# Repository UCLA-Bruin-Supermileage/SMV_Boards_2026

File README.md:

# SMV_Boards_2026
SMV low-voltage projects for 2025-2026

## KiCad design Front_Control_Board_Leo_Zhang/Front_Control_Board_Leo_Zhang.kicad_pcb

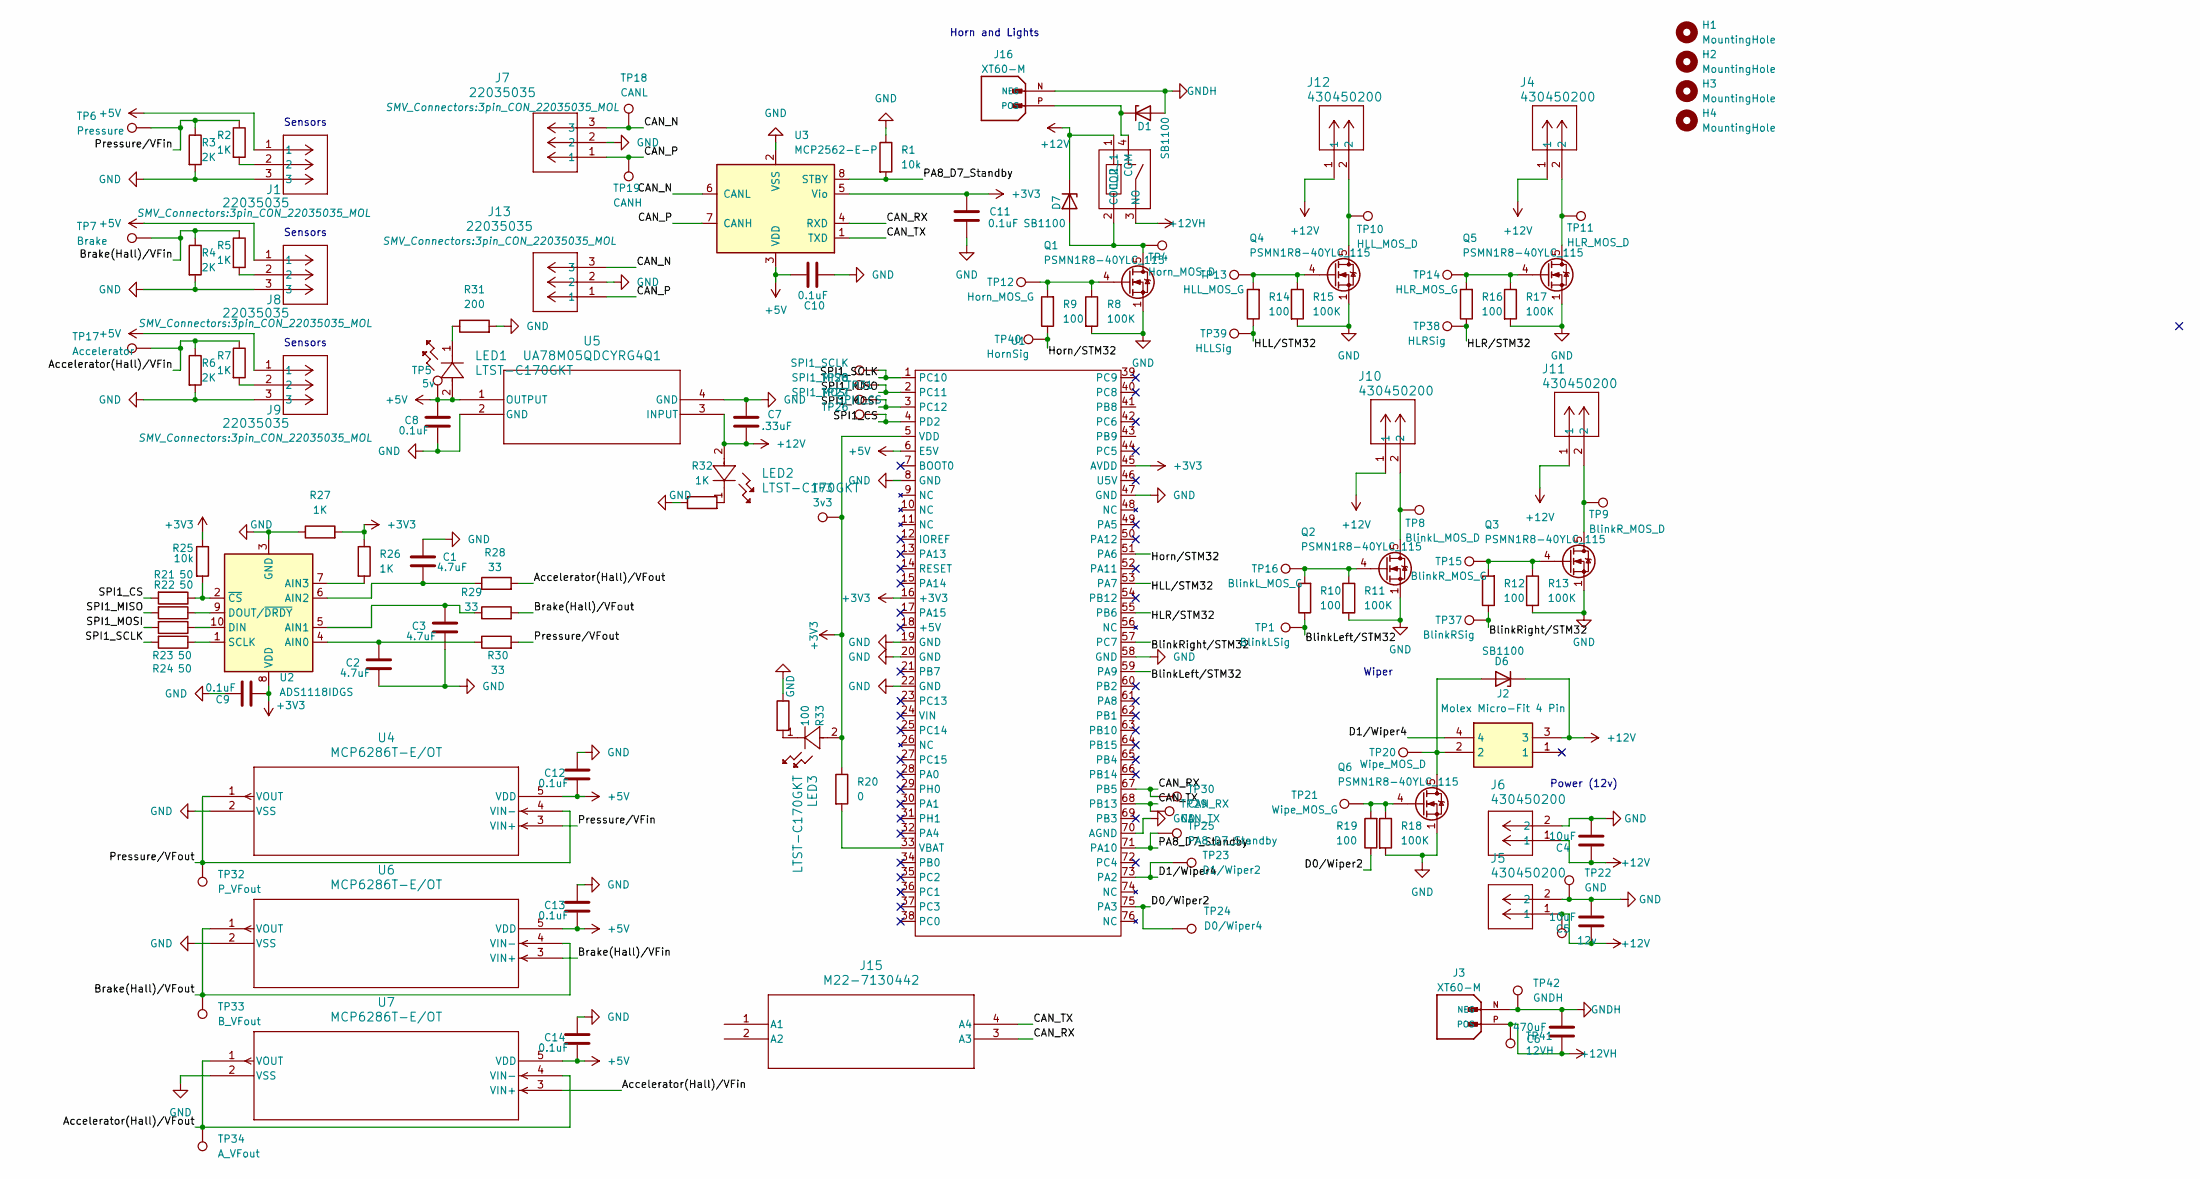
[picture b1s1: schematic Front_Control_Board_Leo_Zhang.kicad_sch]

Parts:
C1, C2, C3: 4.7uF; C_0805_2012Metric
C4, C5: 10uF; CP_Radial_D5.0mm_P2.00mm
C6: 470uF; CP_Radial_D16.0mm_P7.50mm
C7: .33uF; C_0805_2012Metric
C8, C9, C10, C11, C12, C13, C14: 0.1uF; C_0805_2012Metric
D1, D6, D7: SB1100; DO-41_DIO
H1, H2, H3, H4: MountingHole; MountingHole_3.2mm_M3
J1, J7, J8, J9, J13: 22035035; 3pin_CON_22035035_MOL
J2: Molex Micro-Fit 4 Pin; 4_pin0430450401; Manufacturer_Part_Number 0430450401
J3, J16: XT60-M; AMASS_XT60-M; PARTREV V1.2
J4, J5, J6, J10, J11, J12: 430450200; CONN_SD-43045-001_02_MOL
J15: M22-7130442; M22-7130442_TYC
LED1, LED2, LED3: LTST-C170GKT; LED_D3.0mm
Q1, Q2, Q3, Q4, Q5, Q6: PSMN1R8-40YLC_115; LFPAK56_SOT669_NEX
R1, R25: 10k; R_0805_2012Metric
R2, R5, R7, R26, R27, R32: 1K; R_0805_2012Metric
R3, R4, R6: 2K; R_0805_2012Metric
R8, R11, R13, R15, R17, R18: 100K; R_0805_2012Metric
R9, R10, R12, R14, R16, R19, R33: 100; R_0805_2012Metric
R20: 0; R_0805_2012Metric
R21, R22, R23, R24: 50; R_0805_2012Metric
R28, R29, R30: 33; R_0805_2012Metric
R31: 200; R_0805_2012Metric
TP1: BlinkLSig; ValueTestPoint_Pad_D1.0mm
TP2: 12v; ValueTestPoint_Pad_D1.0mm
TP3: 3v3; ValueTestPoint_Pad_D1.0mm
TP4: Horn_MOS_D; ValueTestPoint_Pad_D1.0mm
TP5: 5v; ValueTestPoint_Pad_D1.0mm
TP6: Pressure; ValueTestPoint_Pad_D1.0mm
TP7: Brake; ValueTestPoint_Pad_D1.0mm
TP8: BlinkL_MOS_D; ValueTestPoint_Pad_D1.0mm
TP9: BlinkR_MOS_D; ValueTestPoint_Pad_D1.0mm
TP10: HLL_MOS_D; ValueTestPoint_Pad_D1.0mm
TP11: HLR_MOS_D; ValueTestPoint_Pad_D1.0mm
TP12: Horn_MOS_G; ValueTestPoint_Pad_D1.0mm
TP13: HLL_MOS_G; ValueTestPoint_Pad_D1.0mm
TP14: HLR_MOS_G; ValueTestPoint_Pad_D1.0mm
TP15: BlinkR_MOS_G; ValueTestPoint_Pad_D1.0mm
TP16: BlinkL_MOS_G; ValueTestPoint_Pad_D1.0mm
TP17: Accelerator; ValueTestPoint_Pad_D1.0mm
TP18: CANL; ValueTestPoint_Pad_D1.0mm
TP19: CANH; ValueTestPoint_Pad_D1.0mm
TP20: Wipe_MOS_D; ValueTestPoint_Pad_D1.0mm
TP21: Wipe_MOS_G; ValueTestPoint_Pad_D1.0mm
TP22: GND; ValueTestPoint_Pad_D1.0mm
TP23: D1/Wiper2; ValueTestPoint_Pad_D1.0mm
TP24: D0/Wiper4; ValueTestPoint_Pad_D1.0mm
TP25: PA8_D7_Standby; ValueTestPoint_Pad_D1.0mm
TP26: SPI1_MOSI; ValueTestPoint_Pad_D1.0mm
TP27: SPI1_MISO; ValueTestPoint_Pad_D1.0mm
TP28: SPI1_SCLK; ValueTestPoint_Pad_D1.0mm
TP29: CAN_TX; ValueTestPoint_Pad_D1.0mm
TP30: CAN_RX; ValueTestPoint_Pad_D1.0mm
TP31: SPI1_CS; ValueTestPoint_Pad_D1.0mm
TP32: P_VFout; ValueTestPoint_Pad_D1.0mm
TP33: B_VFout; ValueTestPoint_Pad_D1.0mm
TP34: A_VFout; ValueTestPoint_Pad_D1.0mm
TP37: BlinkRSig; ValueTestPoint_Pad_D1.0mm
TP38: HLRSig; ValueTestPoint_Pad_D1.0mm
TP39: HLLSig; ValueTestPoint_Pad_D1.0mm
TP40: HornSig; ValueTestPoint_Pad_D1.0mm
TP41: 12VH; ValueTestPoint_Pad_D1.0mm
TP42: GNDH; ValueTestPoint_Pad_D1.0mm
U1: MODULE_NUCLEO-F446RE
U2: ADS1118IDGS; DGS0010A_N
U3: MCP2562-E-P; SOIC127P600X175-8N
U4, U6, U7: MCP6286T-E/OT; SOT-23-5_MC_MCH
U5: UA78M05QDCYRG4Q1; DCY4_TEX
U8: J115F11AH12VDCS61.5U; J115F11AH12VDCS615U

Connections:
+3V3: C9.2, C11.1, LED3.2, R20.1, R25.1, R26.1, R27.2, TP3.1, U1.5 (VDD), U1.16 (+3V3), U1.45 (AVDD), U2.8 (VDD), U3.5 (Vio)
+5V: C8.1, C10.1, C12.2, C13.2, C14.2, J1.1, J8.1, J9.1, LED1.2, TP5.1, U1.6 (E5V), U3.3 (VDD), U4.5 (VDD), U5.1 (OUTPUT), U6.5 (VDD), U7.5 (VDD)
+12V: C4.1, C5.1, C7.2, D6.1 (K), D7.1 (K), J2.3, J4.1, J5.1, J6.1, J10.1, J11.1, J12.1, LED2.2, TP2.1, U5.3 (INPUT), U8.1 (COIL_1)
+12VH: C6.1, J3.P (POS), TP41.1, U8.3 (NO)
/Accelerator(Hall)/VFin: R6.1, R7.1, TP17.1, U7.3 (VIN+)
/Accelerator(Hall)/VFout: R28.2, TP34.1, U7.1 (VOUT), U7.4 (VIN-)
/BlinkLeft/STM32: R10.1, TP1.1, U1.59 (PA9)
/BlinkRight/STM32: R12.1, TP37.1, U1.57 (PC7)
/Brake(Hall)/VFin: R4.1, R5.1, TP7.1, U6.3 (VIN+)
/Brake(Hall)/VFout: R29.2, TP33.1, U6.1 (VOUT), U6.4 (VIN-)
/CAN_N: J7.3, J13.3, TP18.1, U3.6 (CANL)
/CAN_P: J7.1, J13.1, TP19.1, U3.7 (CANH)
/CAN_RX: J15.3 (A3), TP30.1, U1.67 (PB5), U3.4 (RXD)
/CAN_TX: J15.4 (A4), TP29.1, U1.68 (PB13), U3.1 (TXD)
/D0/Wiper2: R19.1, TP24.1, U1.75 (PA3)
/D1/Wiper4: J2.4, TP23.1, U1.73 (PA2)
/HLL/STM32: R14.1, TP39.1, U1.53 (PA7)
/HLR/STM32: R16.1, TP38.1, U1.55 (PB6)
/Horn/STM32: R9.1, TP40.1, U1.51 (PA6)
/PA8_D7_Standby: R1.2, TP25.1, U1.71 (PA10), U3.8 (STBY)
/Pressure/VFin: R2.1, R3.1, TP6.1, U4.3 (VIN+)
/Pressure/VFout: R30.2, TP32.1, U4.1 (VOUT), U4.4 (VIN-)
/SPI1_CS: R21.2, TP31.1, U1.4 (PD2)
/SPI1_MISO: R22.2, TP27.1, U1.2 (PC11)
/SPI1_MOSI: R23.2, TP26.1, U1.3 (PC12)
/SPI1_SCLK: R24.2, TP28.1, U1.1 (PC10)
GND: C1.1, C2.2, C3.2, C4.2, C5.2, C7.1, C8.2, C9.1, C10.2, C11.2, C12.1, C13.1, C14.1, J1.3, J5.2, J6.2, J7.2, J8.3, J9.3, J13.2, Q1.1 (S), Q1.2 (S), Q1.3 (S), Q2.1 (S), Q2.2 (S), Q2.3 (S), Q3.1 (S), Q3.2 (S), Q3.3 (S), Q4.1 (S), Q4.2 (S), Q4.3 (S), Q5.1 (S), Q5.2 (S), Q5.3 (S), Q6.1 (S), Q6.2 (S), Q6.3 (S), R1.1, R3.2, R4.2, R6.2, R8.2, R11.2, R13.2, R15.2, R17.2, R18.2, R27.1, R31.2, R32.1, R33.1, TP22.1, U1.8 (GND), U1.19 (GND), U1.20 (GND), U1.22 (GND), U1.47 (GND), U1.58 (GND), U1.70 (AGND), U2.3 (GND), U3.2 (VSS), U4.2 (VSS), U5.2 (GND), U5.4 (GND), U6.2 (VSS), U7.2 (VSS)
GNDH: C6.2, D1.2 (A), J3.N (NEG), J16.N (NEG), TP42.1
unnamed: D1.1 (K), J16.P (POS), U8.4 (COM)
unnamed: D6.2 (A), J2.2, Q6.5 (D), TP20.1
unnamed: D7.2 (A), Q1.5 (D), TP4.1, U8.2 (COIL_2)
unnamed: J1.2, R2.2
unnamed: J8.2, R5.2
unnamed: J9.2, R7.2
unnamed: LED1.1, R31.1
unnamed: LED2.1, R32.2
unnamed: LED3.1, R33.2
unnamed: Q1.4 (G), R8.1, R9.2, TP12.1
unnamed: J10.2, Q2.5 (D), TP8.1
unnamed: Q2.4 (G), R10.2, R11.1, TP16.1
unnamed: J11.2, Q3.5 (D), TP9.1
unnamed: Q3.4 (G), R12.2, R13.1, TP15.1
unnamed: J12.2, Q4.5 (D), TP10.1
unnamed: Q4.4 (G), R14.2, R15.1, TP13.1
unnamed: J4.2, Q5.5 (D), TP11.1
unnamed: Q5.4 (G), R16.2, R17.1, TP14.1
unnamed: Q6.4 (G), R18.1, R19.2, TP21.1
unnamed: R20.2, U1.33 (VBAT)
unnamed: C2.1, R30.1, U2.4 (AIN0)
unnamed: C3.1, R29.1, U2.5 (AIN1)
unnamed: C1.2, R28.1, U2.6 (AIN2)
unnamed: R26.2, U2.7 (AIN3)
unnamed: R23.1, U2.10 (DIN)
unnamed: R22.1, U2.9 (DOUT/~DRDY)
unnamed: R24.1, U2.1 (SCLK)
unnamed: R21.1, R25.2, U2.2 (~CS)

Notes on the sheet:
Power (12v)
Sensors
Wiper
Horn and Lights

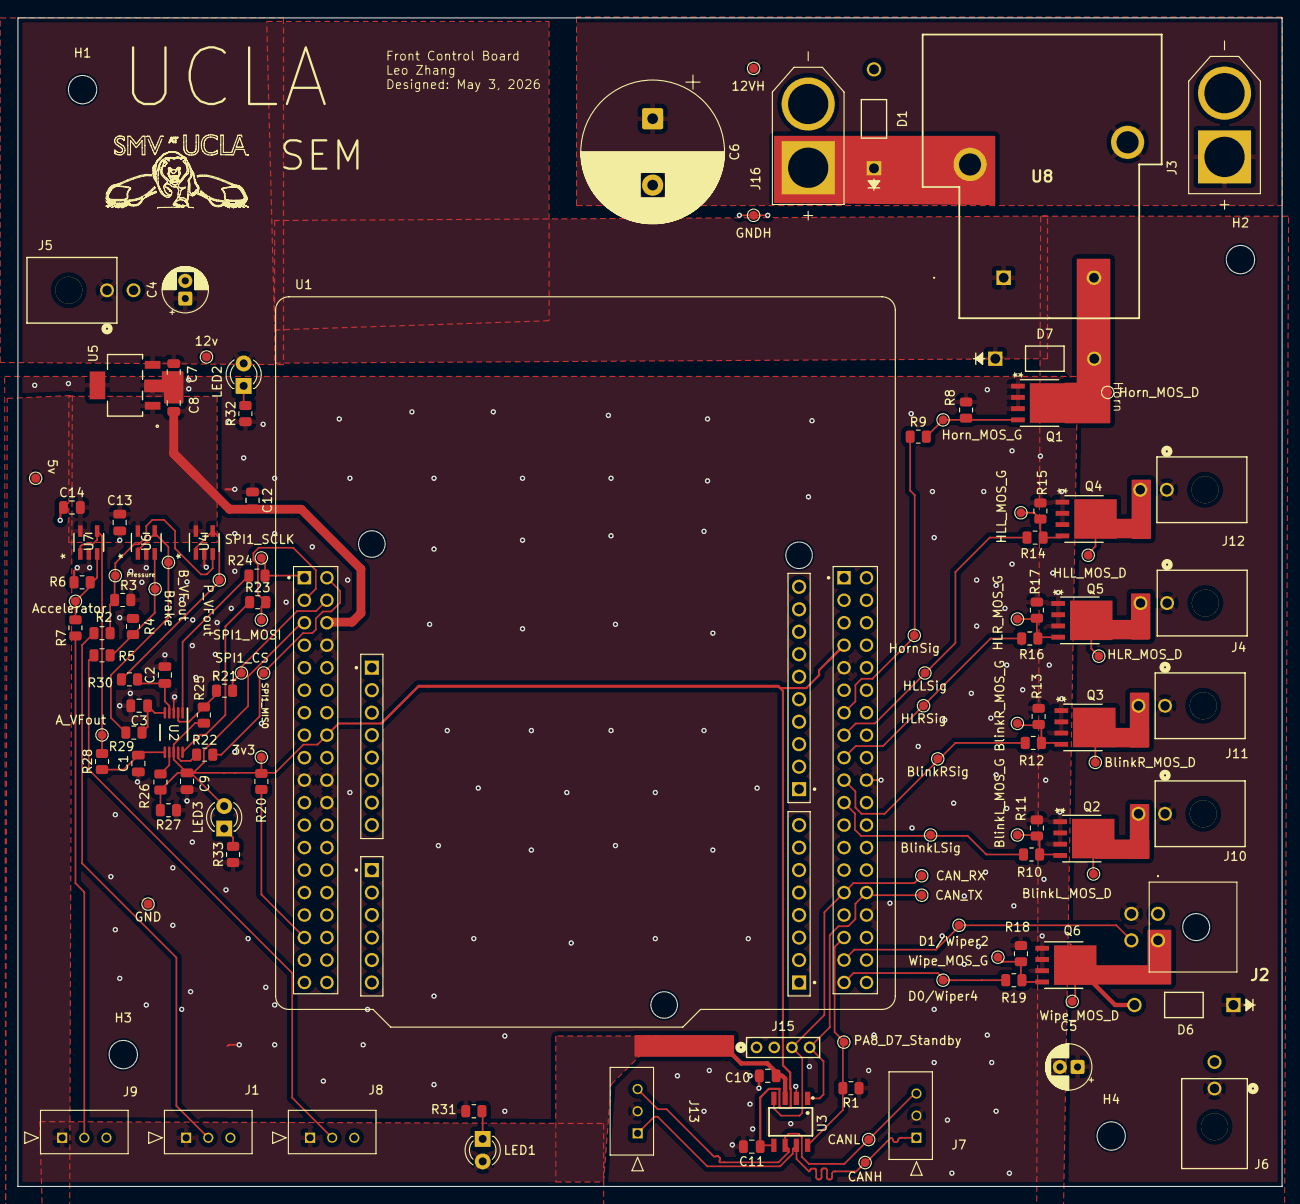
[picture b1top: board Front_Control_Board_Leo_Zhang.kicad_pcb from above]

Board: 2 copper layers, 142.8 x 132.0 mm, 126 parts (0 on the bottom side), 56 nets.

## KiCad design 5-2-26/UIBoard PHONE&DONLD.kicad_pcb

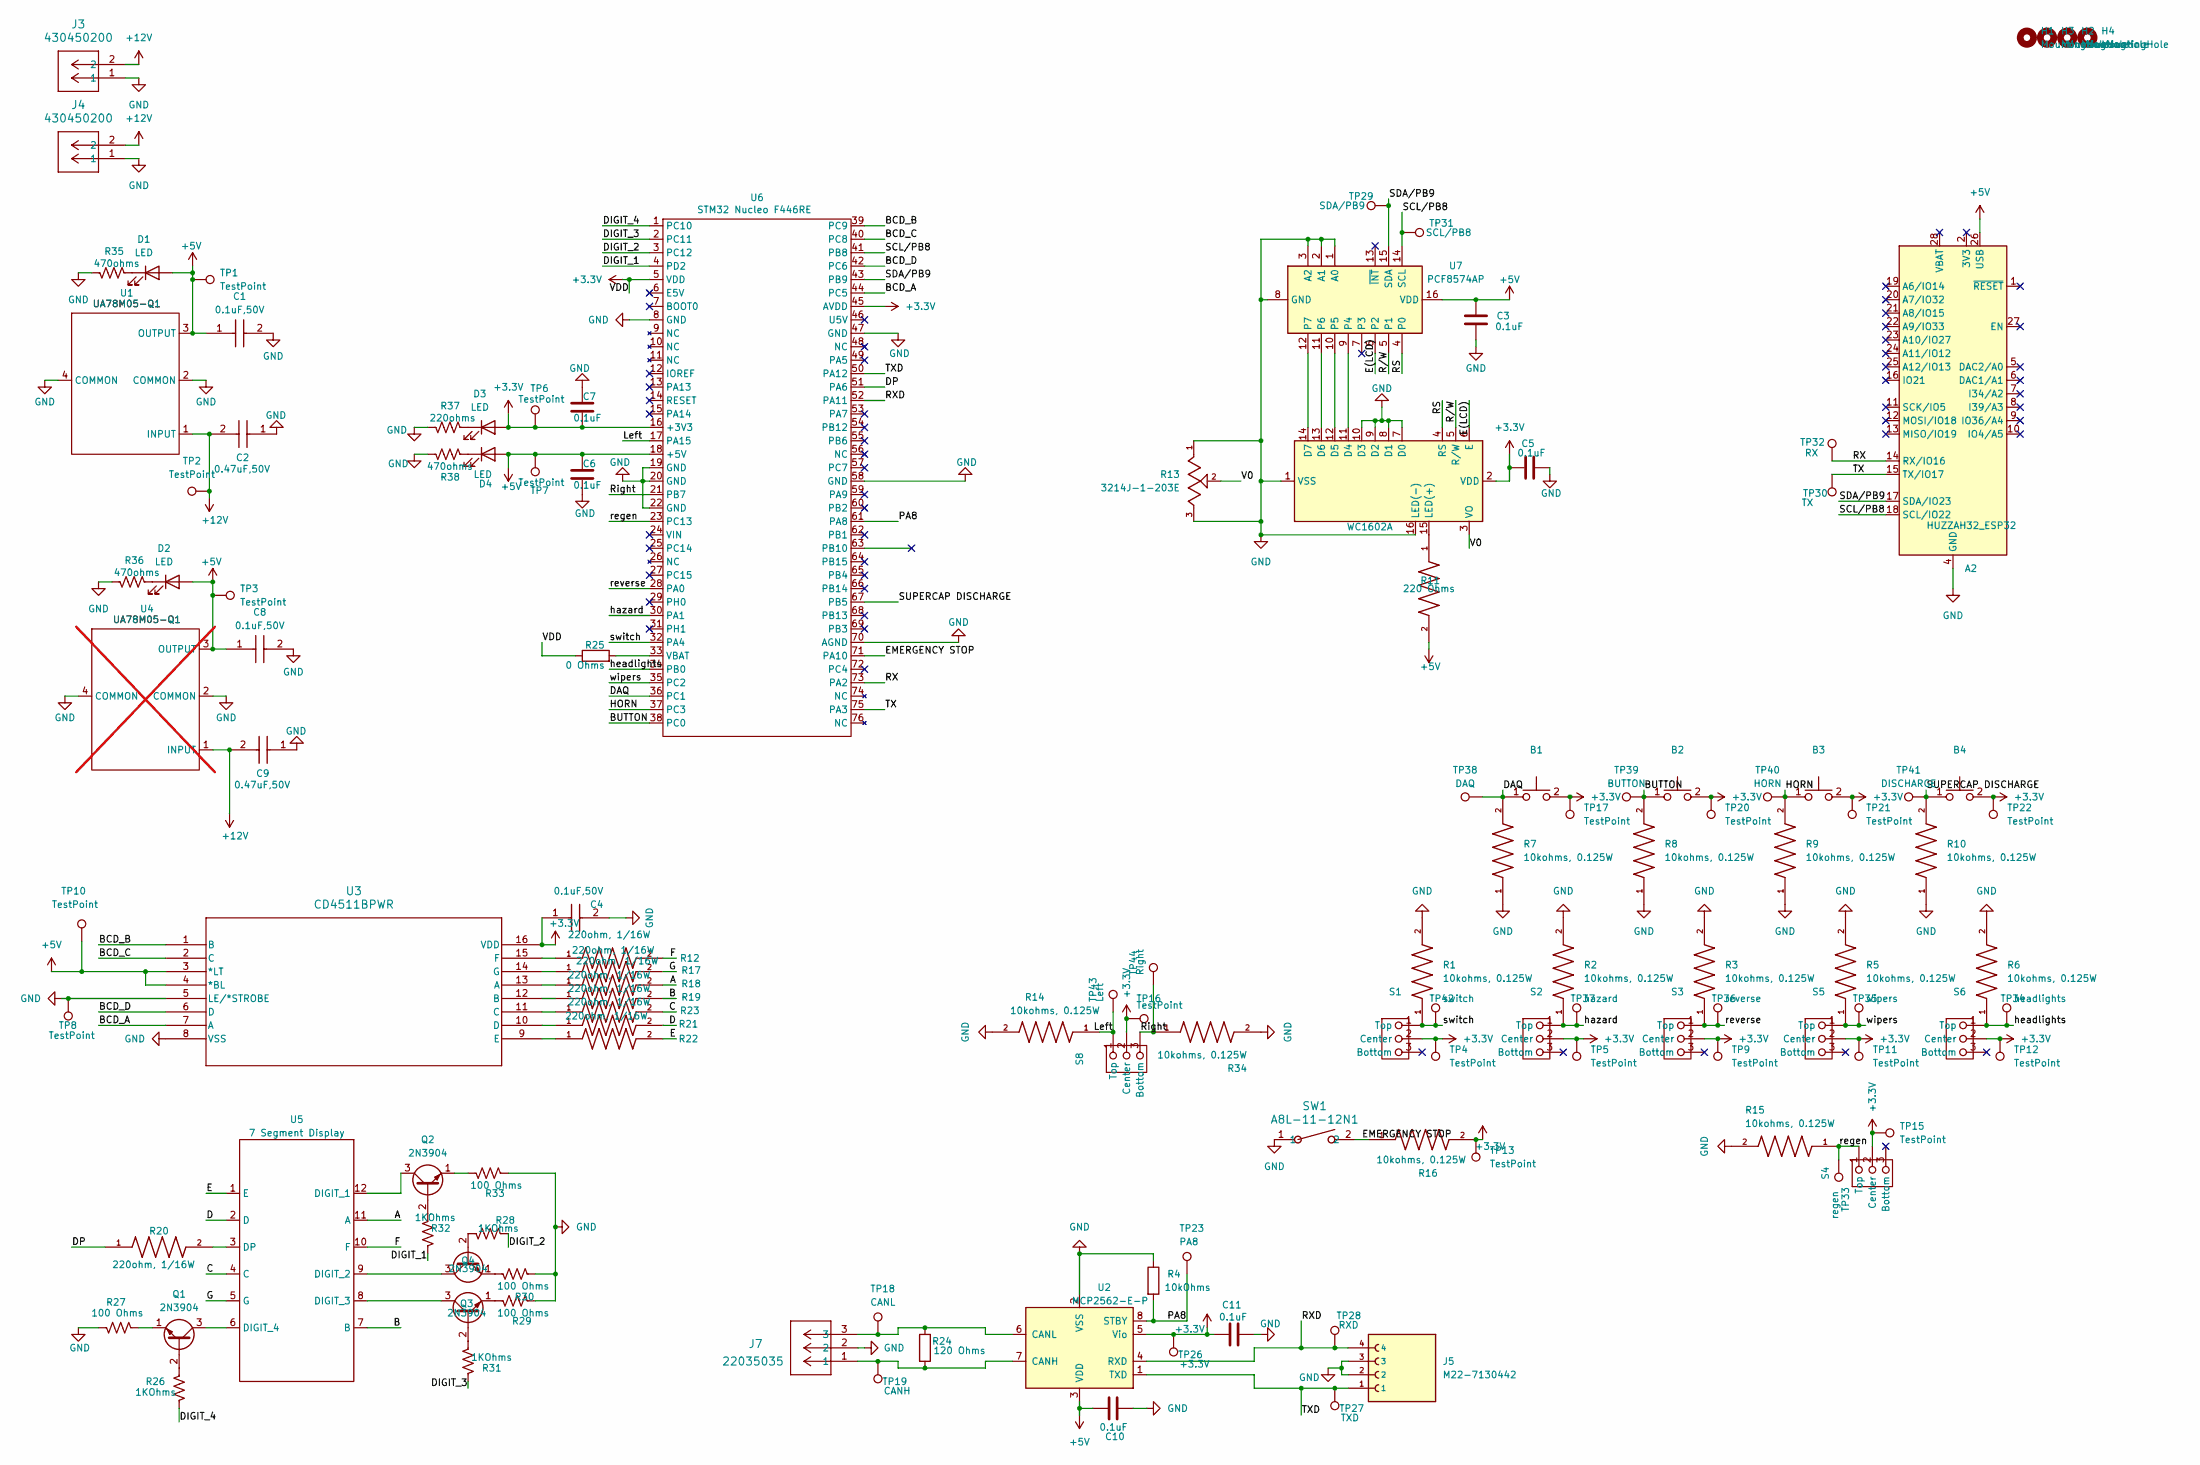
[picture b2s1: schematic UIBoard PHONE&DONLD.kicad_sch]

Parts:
A2: HUZZAH32_ESP32; Adafruit_Feather
B1, B2, B3, B4: Twidec Button
C1, C4, C8: 0.1uF,50V; Cap0805; Manufacturer_Part_Number C0805C104K5RACTU; Mouser Part Number 80-C0805C104K5R
C2, C9: 0.47uF,50V; Cap0805; Manufacturer_Part_Number C0805C334K5RACTU; Mouser Part Number 80-C0805C334K5R
C3, C5, C6, C7, C10, C11: 0.1uF; Cap0805
D1, D2, D3, D4: LED; LED_D3.0mm
DS1: WC1602A
H1, H2, H3, H4: MountingHole; MountingHole_3.2mm_M3
J3, J4: 430450200; CONN_SD-43045-001_02_MOL
J5: M22-7130442; HARWIN_M22-7130442
J7: 22035035; 3pin_CON_22035035_MOL
Q1, Q2, Q3, Q4: 2N3904; TO-92_Inline
R1, R2, R3, R5, R6, R7, R8, R9, R10, R14, R15, R16, R34: 10kohms, 0.125W; 0805RESC2012X60N
R4: 10kOhms; 0805RESC2012X60N
R11: 220 Ohms; 0805RESC2012X60N
R12, R17, R18, R19, R20, R21, R22, R23: 220ohm, 1/16W; 0805RESC2012X60N
R13: 3214J-1-203E; TRIM_3214J-1-203E; PARTREV 06/24
R24: 120 Ohms; 0805RESC2012X60N
R25: 0 Ohms; 0805RESC2012X60N
R26, R28, R31, R32: 1KOhms; 0805RESC2012X60N
R27, R29, R30, R33: 100 Ohms; 0805RESC2012X60N
R35, R36, R38: 470ohms; 0805RESC2012X60N
R37: 220ohms; 0805RESC2012X60N
S1, S2, S3, S4, S5, S6, S8: TAISS 3 Pin Switch
SW1: A8L-11-12N1; SW_A8L-11_OMR
TP1, TP2, TP3, TP4, TP5, TP6, TP7, TP8, TP9, TP10, TP11, TP12, TP13, TP15, TP16, TP17, TP20, TP21, TP22: TestPoint; TestPoint_Pad_2.5x2.5mm
TP18: CANL; TestPoint_Pad_D1.0mm
TP19: CANH; TestPoint_Pad_D1.0mm
TP23: PA8; TestPoint_Pad_D1.0mm
TP26: +3.3V; TestPoint_Pad_D1.0mm
TP27: TXD; TestPoint_Pad_D1.0mm
TP28: RXD; TestPoint_Pad_D1.0mm
TP29: SDA/PB9; TestPoint_Pad_D1.0mm
TP30: TX; TestPoint_Pad_D1.0mm
TP31: SCL/PB8; TestPoint_Pad_D1.0mm
TP32: RX; TestPoint_Pad_D1.0mm
TP33: regen; TestPoint_Pad_2.5x2.5mm
TP34: headlights; TestPoint_Pad_2.5x2.5mm
TP35: wipers; TestPoint_Pad_2.5x2.5mm
TP36: reverse; TestPoint_Pad_2.5x2.5mm
TP37: hazard; TestPoint_Pad_2.5x2.5mm
TP38: DAQ; TestPoint_Pad_2.5x2.5mm
TP39: BUTTON; TestPoint_Pad_2.5x2.5mm
TP40: HORN; TestPoint_Pad_2.5x2.5mm
TP41: DISCHARGE; TestPoint_Pad_2.5x2.5mm
TP42: switch; TestPoint_Pad_2.5x2.5mm
TP43: Left; TestPoint_Pad_2.5x2.5mm
TP44: Right; TestPoint_Pad_2.5x2.5mm
U1: UA78M05-Q1; SOT230P700X180-4N
U2: MCP2562-E-P; SOIC127P600X175-8N
U3: CD4511BPWR
U4: UA78M05-Q1; SOT230P700X180-4N; not fitted
U5: 7 Segment Display; Seven_Seg_display
U6: STM32 Nucleo F446RE; MODULE_NUCLEO-F446RE
U7: PCF8574AP; DIP-16_W7.62mm

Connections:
+3.3V: B1.2, B2.2, B3.2, B4.2, C4.1, C5.1, C7.2, C11.1, D3.2 (A), DS1.2 (VDD), R16.2, R25.1, S1.2 (Center), S2.2 (Center), S3.2 (Center), S4.2 (Center), S5.2 (Center), S6.2 (Center), S8.2 (Center), TP4.1 (1_1), TP5.1 (1_1), TP6.1 (1_1), TP9.1 (1_1), TP11.1 (1_1), TP12.1 (1_1), TP13.1 (1_1), TP15.1 (1_1), TP16.1 (1_1), TP17.1 (1_1), TP20.1 (1_1), TP21.1 (1_1), TP22.1 (1_1), TP26.1 (1_1), U2.5 (Vio), U3.16 (VDD), U6.5 (VDD), U6.16 (+3V3), U6.45 (AVDD)
+5V: A2.26 (USB), C1.1, C3.1, C6.1, C8.1, C10.1, D1.2 (A), D2.2 (A), D4.2 (A), R11.2, TP1.1 (1_1), TP3.1 (1_1), TP7.1 (1_1), TP10.1 (1_1), U1.3 (OUTPUT), U2.3 (VDD), U3.3 (*LT), U3.4 (*BL), U4.3 (OUTPUT), U6.18 (+5V), U7.16 (VDD)
+12V: C2.2, C9.2, J3.2, J4.2, TP2.1 (1_1), U1.1 (INPUT), U4.1 (INPUT)
/A: R18.2, U5.11 (A)
/B: R19.2, U5.7 (B)
/BCD_A: U3.7 (A), U6.44 (PC5)
/BCD_B: U3.1 (B), U6.39 (PC9)
/BCD_C: U3.2 (C), U6.40 (PC8)
/BCD_D: U3.6 (D), U6.42 (PC6)
/BUTTON: B2.1, R8.2, TP39.1 (1_1), U6.38 (PC0)
/C: R23.2, U5.4 (C)
/D: R21.2, U5.2 (D)
/DAQ: B1.1, R7.2, TP38.1 (1_1), U6.36 (PC1)
/DIGIT_1: R32.1, U6.4 (PD2)
/DIGIT_2: R28.1, U6.3 (PC12)
/DIGIT_3: R31.1, U6.2 (PC11)
/DIGIT_4: R26.2, U6.1 (PC10)
/DP: R20.1, U6.51 (PA6)
/E: R22.2, U5.1 (E)
/E(LCD): DS1.6 (E), U7.6 (P2)
/EMERGENCY STOP: R16.1, SW1.2, U6.71 (PA10)
/F: R12.2, U5.10 (F)
/G: R17.2, U5.5 (G)
/HORN: B3.1, R9.2, TP40.1 (1_1), U6.37 (PC3)
/Left: R14.1, S8.1 (Top), TP43.1 (1_1), U6.17 (PA15)
/PA8: R4.2, TP23.1 (1_1), U2.8 (STBY), U6.61 (PA8)
/RS: DS1.4 (RS), U7.4 (P0)
/RX: A2.14 (RX/IO16), TP32.1 (1_1), U6.73 (PA2)
/RXD: J5.4, TP28.1 (1_1), U2.4 (RXD), U6.52 (PA11)
/Right: R34.1, S8.3 (Bottom), TP44.1 (1_1), U6.21 (PB7)
/R/W: DS1.5 (R/W), U7.5 (P1)
/SCL/PB8: A2.18 (SCL/IO22), TP31.1 (1_1), U6.41 (PB8), U7.14 (SCL)
/SDA/PB9: A2.17 (SDA/IO23), TP29.1 (1_1), U6.43 (PB9), U7.15 (SDA)
/SUPERCAP DISCHARGE: B4.1, R10.2, TP41.1 (1_1), U6.67 (PB5)
/TX: A2.15 (TX/IO17), TP30.1 (1_1), U6.75 (PA3)
/TXD: J5.1, TP27.1 (1_1), U2.1 (TXD), U6.50 (PA12)
/V0: DS1.3 (VO), R13.2
/hazard: R2.1, S2.1 (Top), TP37.1 (1_1), U6.30 (PA1)
/headlights: R6.1, S6.1 (Top), TP34.1 (1_1), U6.34 (PB0)
/regen: R15.1, S4.1 (Top), TP33.1 (1_1), U6.23 (PC13)
/reverse: R3.1, S3.1 (Top), TP36.1 (1_1), U6.28 (PA0)
/switch: R1.1, S1.1 (Top), TP42.1 (1_1), U6.32 (PA4)
/wipers: R5.1, S5.1 (Top), TP35.1 (1_1), U6.35 (PC2)
GND: A2.4 (GND), C1.2, C2.1, C3.2, C4.2, C5.2, C6.2, C7.1, C8.2, C9.1, C10.2, C11.2, DS1.1 (VSS), DS1.7 (D0), DS1.8 (D1), DS1.9 (D2), DS1.10 (D3), DS1.16 (LED(-)), J3.1, J4.1, J5.2, J5.3, J7.2, R1.2, R2.2, R3.2, R4.1, R5.2, R6.2, R7.1, R8.1, R9.1, R10.1, R13.1, R13.3, R14.2, R15.2, R27.2, R29.2, R30.2, R33.2, R34.2, R35.2, R36.2, R37.2, R38.2, SW1.1, TP8.1 (1_1), U1.2 (COMMON), U1.4 (COMMON), U2.2 (VSS), U3.5 (LE/*STROBE), U3.8 (VSS), U4.2 (COMMON), U4.4 (COMMON), U6.8 (GND), U6.19 (GND), U6.20 (GND), U6.22 (GND), U6.47 (GND), U6.58 (GND), U6.70 (AGND), U7.1 (A0), U7.2 (A1), U7.3 (A2), U7.8 (GND)
unnamed: D1.1 (K), R35.1
unnamed: D2.1 (K), R36.1
unnamed: D3.1 (K), R37.1
unnamed: D4.1 (K), R38.1
unnamed: DS1.11 (D4), U7.9 (P4)
unnamed: DS1.12 (D5), U7.10 (P5)
unnamed: DS1.13 (D6), U7.11 (P6)
unnamed: DS1.14 (D7), U7.12 (P7)
unnamed: DS1.15 (LED(+)), R11.1
unnamed: Q1.2 (B), R26.1
unnamed: Q1.3 (C), U5.6 (DIGIT_4)
unnamed: Q1.1 (E), R27.1
unnamed: Q2.2 (B), R32.2
unnamed: Q2.3 (C), U5.12 (DIGIT_1)
unnamed: Q2.1 (E), R33.1
unnamed: Q3.2 (B), R31.2
unnamed: Q3.3 (C), U5.8 (DIGIT_3)
unnamed: Q3.1 (E), R29.1
unnamed: Q4.2 (B), R28.2
unnamed: Q4.3 (C), U5.9 (DIGIT_2)
unnamed: Q4.1 (E), R30.1
unnamed: R18.1, U3.13 (A)
unnamed: R19.1, U3.12 (B)
unnamed: R21.1, U3.10 (D)
unnamed: R23.1, U3.11 (C)
unnamed: J7.1, R24.2, TP19.1 (1_1), U2.7 (CANH)
unnamed: J7.3, R24.1, TP18.1 (1_1), U2.6 (CANL)
unnamed: R22.1, U3.9 (E)
unnamed: R12.1, U3.15 (F)
unnamed: R17.1, U3.14 (G)
unnamed: R20.2, U5.3 (DP)
unnamed: R25.2, U6.33 (VBAT)

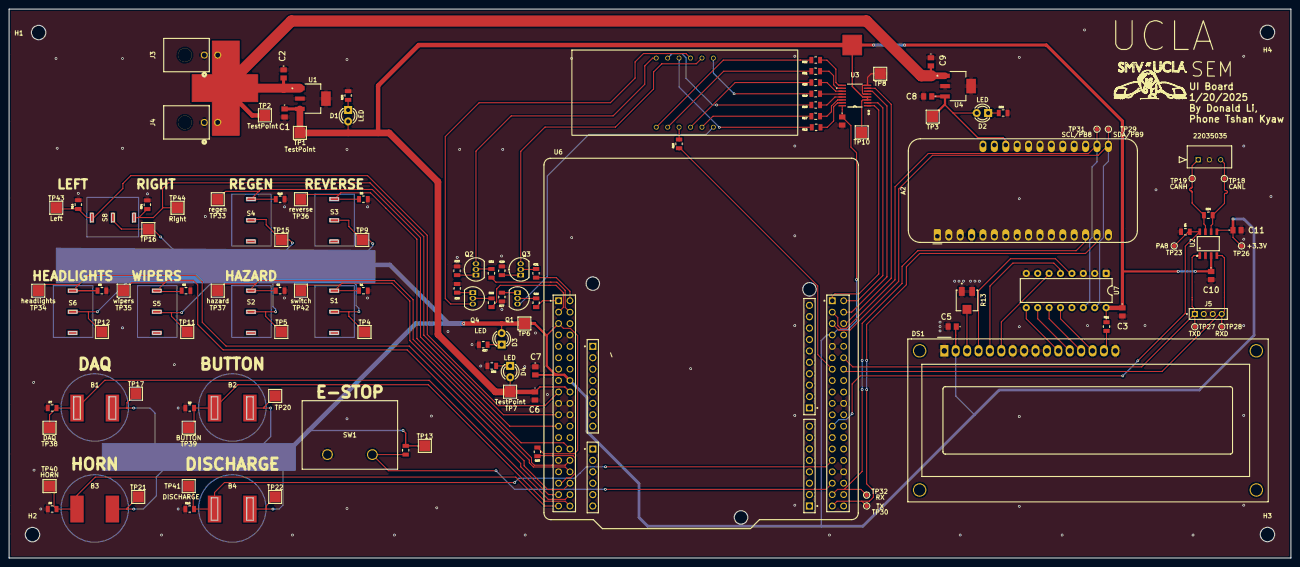
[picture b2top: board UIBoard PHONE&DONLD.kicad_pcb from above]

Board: 2 copper layers, 285.5 x 122.3 mm, 127 parts (0 on the bottom side), 76 nets.

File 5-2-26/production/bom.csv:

Designator,Footprint,Quantity,Value,LCSC Part #
A2,Adafruit_Feather,1,HUZZAH32_ESP32,
"B1, B2, B3, B4",Twidec Button,4,~,
"C1, C4, C8",Cap0805,3,"0.1uF,50V",
"C10, C11, C3, C5, C6, C7",Cap0805,6,0.1uF,
"C2, C9",Cap0805,2,"0.47uF,50V",
"D1, D2, D3, D4",LED_D3.0mm,4,LED,
DS1,WC1602A,1,WC1602A,
"J3, J4",CONN_SD-43045-001_02_MOL,2,430450200,
J5,HARWIN_M22-7130442,1,M22-7130442,
J7,3pin_CON_22035035_MOL,1,22035035,
"Q1, Q2, Q3, Q4",TO-92_Inline,4,2N3904,
"R1, R10, R14, R15, R16, R2, R3, R34, R5, R6, R7, R8, R9",0805RESC2012X60N,13,"10kohms, 0.125W",
R11,0805RESC2012X60N,1,220 Ohms,
"R12, R17, R18, R19, R20, R21, R22, R23",0805RESC2012X60N,8,"220ohm, 1/16W",
R13,TRIM_3214J-1-203E,1,3214J-1-203E,
R24,0805RESC2012X60N,1,120 Ohms,
R25,0805RESC2012X60N,1,0 Ohms,
"R26, R28, R31, R32",0805RESC2012X60N,4,1KOhms,
"R27, R29, R30, R33",0805RESC2012X60N,4,100 Ohms,
"R35, R36, R38",0805RESC2012X60N,3,470ohms,
R37,0805RESC2012X60N,1,220ohms,
R4,0805RESC2012X60N,1,10kOhms,
"S1, S2, S3, S4, S5, S6, S8",TAISS 3 Pin Switch,7,~,
SW1,SW_A8L-11_OMR,1,A8L-11-12N1,
"TP1, TP10, TP11, TP12, TP13, TP15, TP16, TP17, TP2, TP20, TP21, TP22, TP3, TP4, TP5, TP6, TP7, TP8, TP9",TestPoint_Pad_2.5x2.5mm,19,TestPoint,
TP18,TestPoint_Pad_D1.0mm,1,CANL,
TP19,TestPoint_Pad_D1.0mm,1,CANH,
TP23,TestPoint_Pad_D1.0mm,1,PA8,
TP26,TestPoint_Pad_D1.0mm,1,+3.3V,
TP27,TestPoint_Pad_D1.0mm,1,TXD,
TP28,TestPoint_Pad_D1.0mm,1,RXD,
TP29,TestPoint_Pad_D1.0mm,1,SDA/PB9,
TP30,TestPoint_Pad_D1.0mm,1,TX,
TP31,TestPoint_Pad_D1.0mm,1,SCL/PB8,
TP32,TestPoint_Pad_D1.0mm,1,RX,
TP33,TestPoint_Pad_2.5x2.5mm,1,regen,
TP34,TestPoint_Pad_2.5x2.5mm,1,headlights,
TP35,TestPoint_Pad_2.5x2.5mm,1,wipers,
TP36,TestPoint_Pad_2.5x2.5mm,1,reverse,
TP37,TestPoint_Pad_2.5x2.5mm,1,hazard,
TP38,TestPoint_Pad_2.5x2.5mm,1,DAQ,
TP39,TestPoint_Pad_2.5x2.5mm,1,BUTTON,
TP40,TestPoint_Pad_2.5x2.5mm,1,HORN,
TP41,TestPoint_Pad_2.5x2.5mm,1,DISCHARGE,
TP42,TestPoint_Pad_2.5x2.5mm,1,switch,
TP43,TestPoint_Pad_2.5x2.5mm,1,Left,
TP44,TestPoint_Pad_2.5x2.5mm,1,Right,
"U1, U4",SOT230P700X180-4N,2,UA78M05-Q1,
U2,SOIC127P600X175-8N,1,MCP2562-E-P,
U3,CD4511BPWR,1,CD4511BPWR,
U5,Seven_Seg_display,1,7 Segment Display,
U6,MODULE_NUCLEO-F446RE,1,STM32 Nucleo F446RE,
U7,DIP-16_W7.62mm,1,PCF8574AP,

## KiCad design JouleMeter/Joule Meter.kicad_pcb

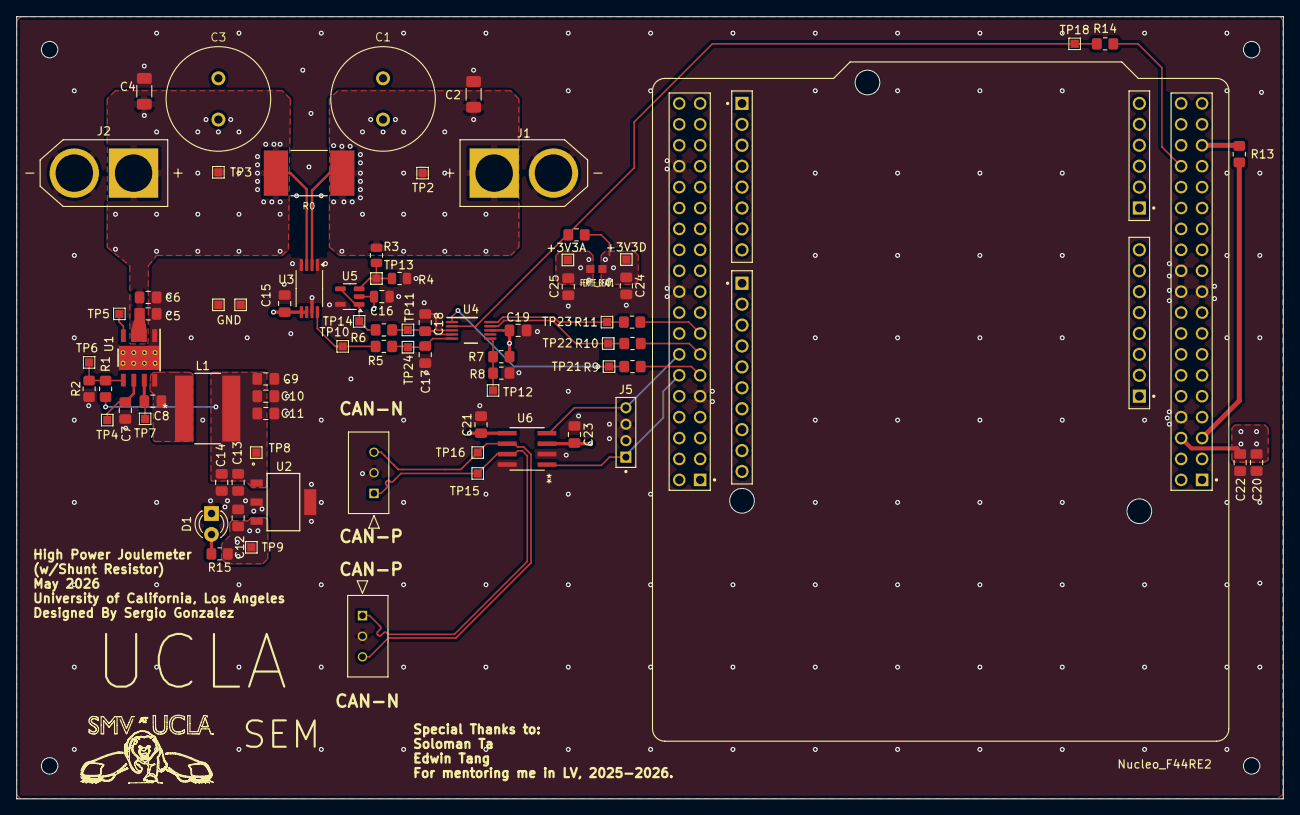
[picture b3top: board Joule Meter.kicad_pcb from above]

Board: 4 copper layers, 153.8 x 95.0 mm, 80 parts (0 on the bottom side), 33 nets.

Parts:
+3V3A: POWER-3V3A; TestPoint_Pad_1.0x1.0mm
+3V3D: POWER-3V3D; TestPoint_Pad_1.0x1.0mm
C1, C3: 470uF, 63V; Big_Chunky_Cap
C2, C4: 10μF; C_1206_3216Metric_Pad1.33x1.80mm_HandSolder
C5: 220nF; C_0805_2012Metric_Pad1.18x1.45mm_HandSolder
C6: 2.2uF; C_0805_2012Metric_Pad1.18x1.45mm_HandSolder
C7, C8, C12, C15, C17, C18, C19, C20, C23, C24, C25: 0.1uF; C_0805_2012Metric_Pad1.18x1.45mm_HandSolder
C9: 0.333uF; C_0805_2012Metric_Pad1.18x1.45mm_HandSolder
C10, C11: 22uF; C_0805_2012Metric_Pad1.18x1.45mm_HandSolder
C13: 0.33uF; C_0805_2012Metric_Pad1.18x1.45mm_HandSolder
C14: 22 uF; C_0805_2012Metric_Pad1.18x1.45mm_HandSolder
C16: 0.1μF; C_0805_2012Metric
C21: 0.1μF; C_0805_2012Metric_Pad1.18x1.45mm_HandSolder
C22: 10uF; C_0805_2012Metric_Pad1.18x1.45mm_HandSolder
D1: Power_LED; LED_D3.0mm
FERITE_BEAD1: FB1; Ferite_Joule
GND: Ground; TestPoint_Pad_1.0x1.0mm
J1, J2: XT60-M; AMASS_XT60-M
J3, J4: 22035035; 3pin_CON_22035035_MOL
J5: M22-7130442; HARWIN_M22-7130442
L1: 100uH; IND_BOURNS_SRN8040
Nucleo_F44RE2: MODULE_NUCLEO-F446RE
R0: R_Shunt_US; RESC10052X145N
R1: 100K; R_0805_2012Metric_Pad1.20x1.40mm_HandSolder
R2: 16K; R_0805_2012Metric_Pad1.20x1.40mm_HandSolder
R3: 500k; R_0805_2012Metric
R4: 20k; R_0805_2012Metric
R5, R6: 500; R_0805_2012Metric_Pad1.20x1.40mm_HandSolder
R7, R8: 2k; R_0805_2012Metric_Pad1.20x1.40mm_HandSolder
R9, R10, R11, R14: 50; R_0805_2012Metric_Pad1.20x1.40mm_HandSolder
R12: 5k; R_0805_2012Metric_Pad1.20x1.40mm_HandSolder
R13: 0; R_0805_2012Metric_Pad1.20x1.40mm_HandSolder
R15: 220; R_0805_2012Metric_Pad1.20x1.40mm_HandSolder
TP1: Ground; TestPoint_Pad_1.0x1.0mm
TP2: POWER-48V IN; TestPoint_Pad_1.0x1.0mm
TP3: POWER-48V OUT; TestPoint_Pad_1.0x1.0mm
TP4: BUCK-VCC; TestPoint_Pad_1.0x1.0mm
TP5: BUCK-PG; TestPoint_Pad_1.0x1.0mm
TP6: BUCK-FB; TestPoint_Pad_1.0x1.0mm
TP7: BUCK-BOOT; TestPoint_Pad_1.0x1.0mm
TP8: POWER-7V; TestPoint_Pad_1.0x1.0mm
TP9: POWER-5V; TestPoint_Pad_1.0x1.0mm
TP10: CURRENT-OUT; TestPoint_Pad_1.0x1.0mm
TP11: VF-RC; TestPoint_Pad_1.0x1.0mm
TP12: ADC- 1.6V; TestPoint_Pad_1.0x1.0mm
TP13: VF-V+; TestPoint_Pad_1.0x1.0mm
TP14: VF-V-; TestPoint_Pad_1.0x1.0mm
TP15: CT-RCAN_H; TestPoint_Pad_1.0x1.0mm
TP16: CT-CAN_L; TestPoint_Pad_1.0x1.0mm
TP18: ADC-CS; TestPoint_Pad_1.0x1.0mm
TP21: ADC-SCLK; TestPoint_Pad_1.0x1.0mm
TP22: ADC-MISO; TestPoint_Pad_1.0x1.0mm
TP23: ADC-MOSI; TestPoint_Pad_1.0x1.0mm
TP24: CURRENT-RC; TestPoint_Pad_1.0x1.0mm
U1: LMR36510; DDA0008J
U2: SOT-223_DCY_TEX
U3: INA240A1PW; TSSOP-8_4.4x3mm_P0.65mm
U4: ADS1118IDGS-Q1; DGS0010A_M
U5: MCP6286T-E/OT1; SOT-23-5
U6: MCP2562; SOIC8-N_MC_MCH-M

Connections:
+3V3A: +3V3A.1 (1_1), C15.1, C16.1, C19.2, C21.1, C25.1, FERITE_BEAD1.2, R7.1, U3.5 (V+), U3.6 (REF2), U4.8 (VDD), U5.2 (V+), U6.5 (VIO)
+3V3D: +3V3D.1 (1_1), C24.1, FERITE_BEAD1.1, Nucleo_F44RE2.16 (+3V3), R12.1
+5V: C12.1, C20.1, C22.1, C23.1, Nucleo_F44RE2.6 (E5V), R15.1, TP9.1 (1_1), U2.3 (OUTPUT), U6.3 (VDD)
+7V: C9.1, C10.1, C11.1, C13.1, C14.1, L1.2, R1.2, TP8.1 (1_1), U2.1 (INPUT)
/CAN-TXD: J5.1, Nucleo_F44RE2.50 (PA12), U6.1 (TXD)
/CAN_N: J3.3, J4.3, TP16.1 (1_1), U6.6 (CANL)
/CAN_P: J3.1, J4.1, TP15.1 (1_1), U6.7 (CANH)
/CAN_RXD: J5.4, Nucleo_F44RE2.52 (PA11), U6.4 (RXD)
/CS: R12.2, R14.2, TP18.1 (1_1), U4.2 (~CS)
/Current_Sense: R5.1, TP10.1 (1_1), U3.8
/FB: R1.1, R2.1, TP6.1 (1_1), U1.5 (FB)
/MISO: R10.2, TP22.1 (1_1), U4.9 (DOUT/~DRDY)
/MOSI: R11.2, TP23.1 (1_1), U4.10 (DIN)
/Nucleo_F446RE/NUCLEO_1: Nucleo_F44RE2.5 (VDD), R13.2
/SCLK: R9.2, TP21.1 (1_1), U4.1 (SCLK)
/Voltage Follower: R6.1, TP14.1 (1_1), U5.1, U5.4 (-)
GND: C2.2, C4.2, C5.1, C6.1, C7.1, C9.2, C10.2, C11.2, C12.2, C13.2, C14.2, C15.2, C16.2, C17.2, C18.1, C19.1, C20.2, C21.2, C22.2, C23.2, C24.2, C25.2, D1.1 (K), GND.1 (1_1), J1.N (NEG), J2.N (NEG), J3.2, J4.2, J5.2, J5.3, Nucleo_F44RE2.8 (GND), Nucleo_F44RE2.19 (GND), Nucleo_F44RE2.20 (GND), Nucleo_F44RE2.22 (GND), Nucleo_F44RE2.47 (GND), Nucleo_F44RE2.58 (GND), Nucleo_F44RE2.70 (AGND), R2.2, R4.2, R8.2, TP1.1, U1.1 (PGND), U1.9 (PAD), U2.2 (COMMON), U2.4 (COMMON), U3.1 (GND), U3.4 (GND), U3.7 (REF1), U4.3 (GND), U5.5 (V-), U6.2 (VSS), U6.8 (STBY)
unnamed: D1.2 (A), R15.2
unnamed: C2.1, J1.P (POS), R0.1, R3.1, TP2.1 (1_1), U3.2 (+)
unnamed: C4.1, C5.2, C6.2, J2.P (POS), R0.2, TP3.1 (1_1), U1.2 (VIN), U1.3 (EN), U3.3 (-)
unnamed: Nucleo_F44RE2.32 (PA4), R14.1
unnamed: Nucleo_F44RE2.49 (PA5), R9.1
unnamed: Nucleo_F44RE2.51 (PA6), R10.1
unnamed: Nucleo_F44RE2.53 (PA7), R11.1
unnamed: Nucleo_F44RE2.33 (VBAT), R13.1
unnamed: C8.1, TP7.1 (1_1), U1.7 (BOOT)
unnamed: TP5.1 (1_1), U1.4 (PG)
unnamed: C8.2, L1.1, U1.8 (SW)
unnamed: C7.2, TP4.1 (1_1), U1.6 (VCC)
unnamed: C18.2, R6.2, TP11.1 (1_1), U4.4 (AIN0)
unnamed: C17.1, R5.2, TP24.1 (1_1), U4.5 (AIN1)
unnamed: R7.2, R8.1, TP12.1 (1_1), U4.6 (AIN2)
unnamed: R3.2, R4.1, TP13.1 (1_1), U5.3 (+)

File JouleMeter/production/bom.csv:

Designator,Footprint,Quantity,Value,LCSC Part #
+3V3A,TestPoint_Pad_1.0x1.0mm,1,POWER-3V3A,
+3V3D,TestPoint_Pad_1.0x1.0mm,1,POWER-3V3D,
"C1, C3",Big_Chunky_Cap,2,"470uF, 63V",
"C10, C11",0805,2,22uF,
"C12, C15, C17, C18, C19, C20, C23, C24, C25, C7, C8",0805,11,0.1uF,
C13,0805,1,0.33uF,
C14,0805,1,22 uF,
"C16, C21",0805,2,0.1μF,
"C2, C4",1206,2,10μF,
C22,0805,1,10uF,
C5,0805,1,220nF,
C6,0805,1,2.2uF,
C9,0805,1,0.333uF,
D1,LED_D3.0mm,1,Power_LED,
FERITE_BEAD1,Ferite_Joule,1,FB1,
"GND, TP1",TestPoint_Pad_1.0x1.0mm,2,Ground,
"J1, J2",AMASS_XT60-M,2,XT60-M,
"J3, J4",3pin_CON_22035035_MOL,2,22035035,
J5,HARWIN_M22-7130442,1,M22-7130442,
L1,IND_BOURNS_SRN8040,1,100uH,
NUCLEO_F44RE2,MODULE_NUCLEO-F446RE,1,~,
R0,RESC10052X145N,1,R_Shunt_US,
R1,0805,1,100K,
"R10, R11, R14, R9",0805,4,50,
R12,0805,1,5k,
R13,0805,1,0,
R15,0805,1,220,
R2,0805,1,16K,
R3,0805,1,500k,
R4,0805,1,20k,
"R5, R6",0805,2,500,
"R7, R8",0805,2,2k,
TP10,TestPoint_Pad_1.0x1.0mm,1,CURRENT-OUT,
TP11,TestPoint_Pad_1.0x1.0mm,1,VF-RC,
TP12,TestPoint_Pad_1.0x1.0mm,1,ADC- 1.6V,
TP13,TestPoint_Pad_1.0x1.0mm,1,VF-V+,
TP14,TestPoint_Pad_1.0x1.0mm,1,VF-V-,
TP15,TestPoint_Pad_1.0x1.0mm,1,CT-RCAN_H,
TP16,TestPoint_Pad_1.0x1.0mm,1,CT-CAN_L,
TP18,TestPoint_Pad_1.0x1.0mm,1,ADC-CS,
TP2,TestPoint_Pad_1.0x1.0mm,1,POWER-48V IN,
TP21,TestPoint_Pad_1.0x1.0mm,1,ADC-SCLK,
TP22,TestPoint_Pad_1.0x1.0mm,1,ADC-MISO,
TP23,TestPoint_Pad_1.0x1.0mm,1,ADC-MOSI,
TP24,TestPoint_Pad_1.0x1.0mm,1,CURRENT-RC,
TP3,TestPoint_Pad_1.0x1.0mm,1,POWER-48V OUT,
TP4,TestPoint_Pad_1.0x1.0mm,1,BUCK-VCC,
TP5,TestPoint_Pad_1.0x1.0mm,1,BUCK-PG,
TP6,TestPoint_Pad_1.0x1.0mm,1,BUCK-FB,
TP7,TestPoint_Pad_1.0x1.0mm,1,BUCK-BOOT,
TP8,TestPoint_Pad_1.0x1.0mm,1,POWER-7V,
TP9,TestPoint_Pad_1.0x1.0mm,1,POWER-5V,
U1,DDA0008J,1,LMR36510,
U2,SOT-223_DCY_TEX,1,~,
U3,TSSOP-8_4.4x3mm_P0.65mm,1,INA240A1PW,
U4,DGS0010A_M,1,ADS1118IDGS-Q1,
U5,SOT-23-5,1,MCP6286T-E/OT1,
U6,SOIC8-N_MC_MCH-M,1,MCP2562,
